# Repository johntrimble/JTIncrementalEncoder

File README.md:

# The JT Incremental Encoder
This is the Arduino source code for an optical rotary incremental encoder I built as a sort of hobby project. It provides 2-channel Quadrature output, as well as an I2C interface for calibration and reading position information.

## Dependencies
- Arduino IDE 1.5 or greater
- MCP4xxx library, available [here](https://github.com/johntrimble/MCP42xxx)
- g++ 4.2 or greater, this is just for the unit tests
- Make
- Git 1.6.5 or greater

## Building
This project uses submodules, so you'll want to do the following when cloning the repository:

```
git clone --recursive git@github.com:johntrimble/JTIncrementalEncoder.git
```

From there, just open the `JTIncrementalEncoder.ino` in the Arduino IDE and build it just like any other Arduino project.

## Unit Testing
Arduino doesn't have much in the way of support for unit testing code. Consequently, in the test folder there is a Makefile for building some native binaries to test the code. To run them, execute the following from the project root:

```
cd test
make
./interface_unittest && ./encoder_unittest
```

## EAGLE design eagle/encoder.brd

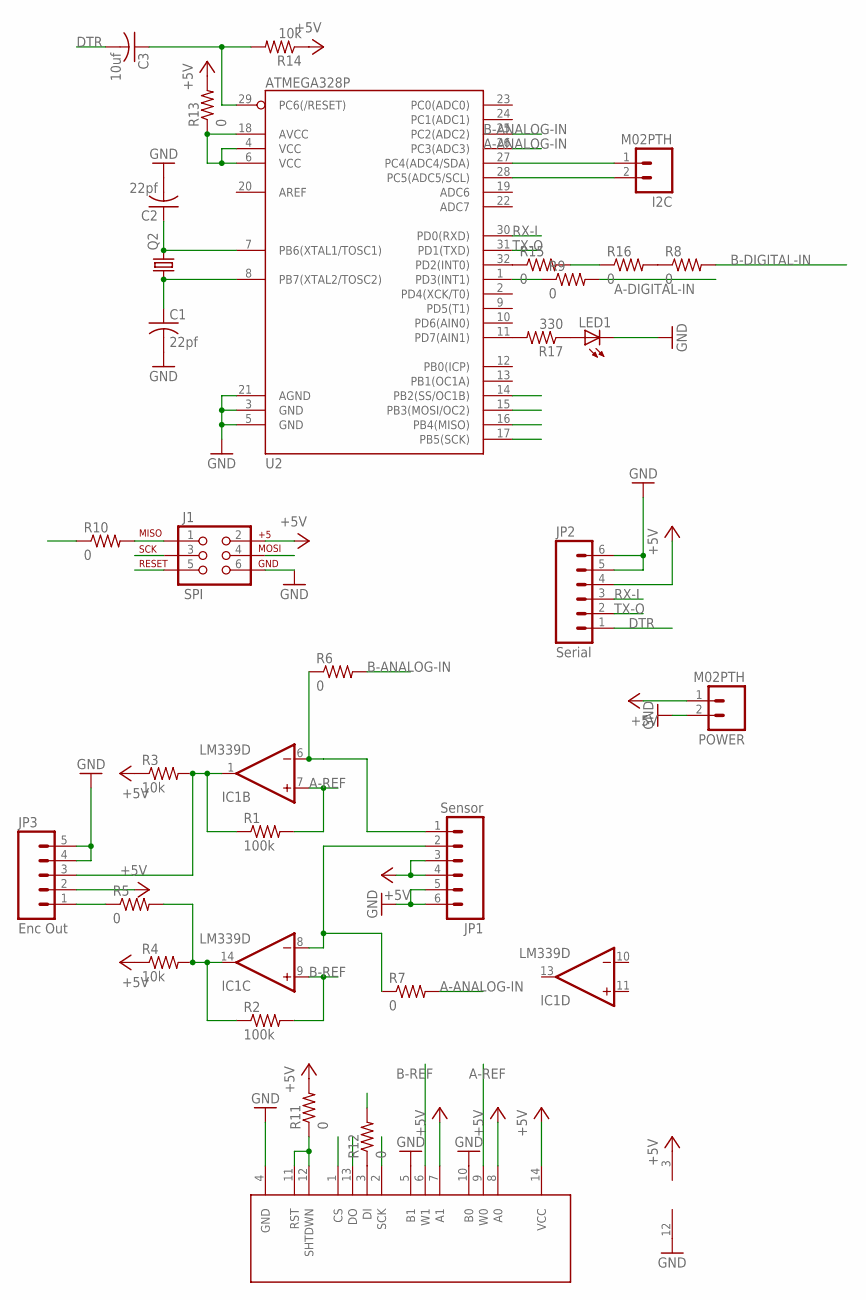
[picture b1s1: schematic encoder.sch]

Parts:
C1, C2: 22pf; C1206
C3: 10uf; C1206
I2C: M02PTH; 1X02
IC1: LM339D; SO14
J1: SPI; 2X3-NS
JP1: Sensor; 1X06
JP2: Serial; 1X06
JP3: Enc Out; 1X05_NO_SILK
LED1: LEDSMT1206; 1206
POWER: M02PTH; 1X02
Q2: CRYSTALHC49UP; HC49UP
R1, R2: 100k; R1206
R3, R4, R14: 10k; R1206
R5, R6, R7, R8, R9, R10, R11, R12, R13, R15, R16: 0; R1206
R17: 330; R1206
U1: MCP42XXX; SO014
U2: ATMEGA328P; TQFP32-08

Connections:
+5V: IC1.3 (V+), J1.2, JP1.3, JP1.4, JP2.4, JP3.2, POWER.1, R3.1, R4.1, R11.2, R13.2, R14.1, U1.7 (A1), U1.8 (A0), U1.14 (VCC)
A-ANALOG-IN: R7.2, U2.26 (PC3(ADC3))
A-DIGITAL-IN: IC1.1 (OUT), JP3.3, R1.1, R3.2, R9.2
A-REF: IC1.7 (+IN), R1.2, U1.9 (W0)
B-ANALOG-IN: R6.2, U2.25 (PC2(ADC2))
B-DIGITAL-IN: JP3.1, R5.1, R8.2
B-REF: IC1.9 (+IN), R2.2, U1.6 (W1)
DTR: C3.2, JP2.1
GND: C1.2, C2.2, IC1.12 (GND), J1.6, JP1.5, JP1.6, JP2.5, JP2.6, JP3.4, JP3.5, LED1.C, POWER.2, U1.4 (GND), U1.5 (B1), U1.10 (B0), U2.3 (GND), U2.5 (GND), U2.21 (AGND)
MISO: R10.1, U1.13 (DO), U2.16 (PB4(MISO))
MOSI: J1.4, R12.2, U2.15 (PB3(MOSI/OC2))
unnamed: IC1.8 (-IN), JP1.2, R7.1
unnamed: J1.1, R10.2
unnamed: IC1.6 (-IN), JP1.1, R6.1
unnamed: R11.1, U1.11 (RST), U1.12 (SHTDWN)
unnamed: IC1.14 (OUT), R2.1, R4.2, R5.2
unnamed: R15.1, U2.32 (PD2(INT0))
unnamed: R9.1, U2.1 (PD3(INT1))
unnamed: R12.1, U1.3 (DI)
unnamed: R13.1, U2.4 (VCC), U2.6 (VCC), U2.18 (AVCC)
unnamed: C1.1, Q2.1, U2.8 (PB7(XTAL2/TOSC2))
unnamed: C2.1, Q2.2, U2.7 (PB6(XTAL1/TOSC1))
unnamed: I2C.1, U2.27 (PC4(ADC4/SDA))
unnamed: I2C.2, U2.28 (PC5(ADC5/SCL))
unnamed: R15.2, R16.1
unnamed: R8.1, R16.2
unnamed: LED1.A, R17.1
unnamed: R17.2, U2.11 (PD7(AIN1))
RESET: C3.1, J1.5, R14.2, U2.29 (PC6(/RESET))
RX-I: JP2.3, U2.30 (PD0(RXD))
SCK: J1.3, U1.2 (SCK), U2.17 (PB5(SCK))
SS: U1.1 (CS), U2.14 (PB2(SS/OC1B))
TX-O: JP2.2, U2.31 (PD1(TXD))

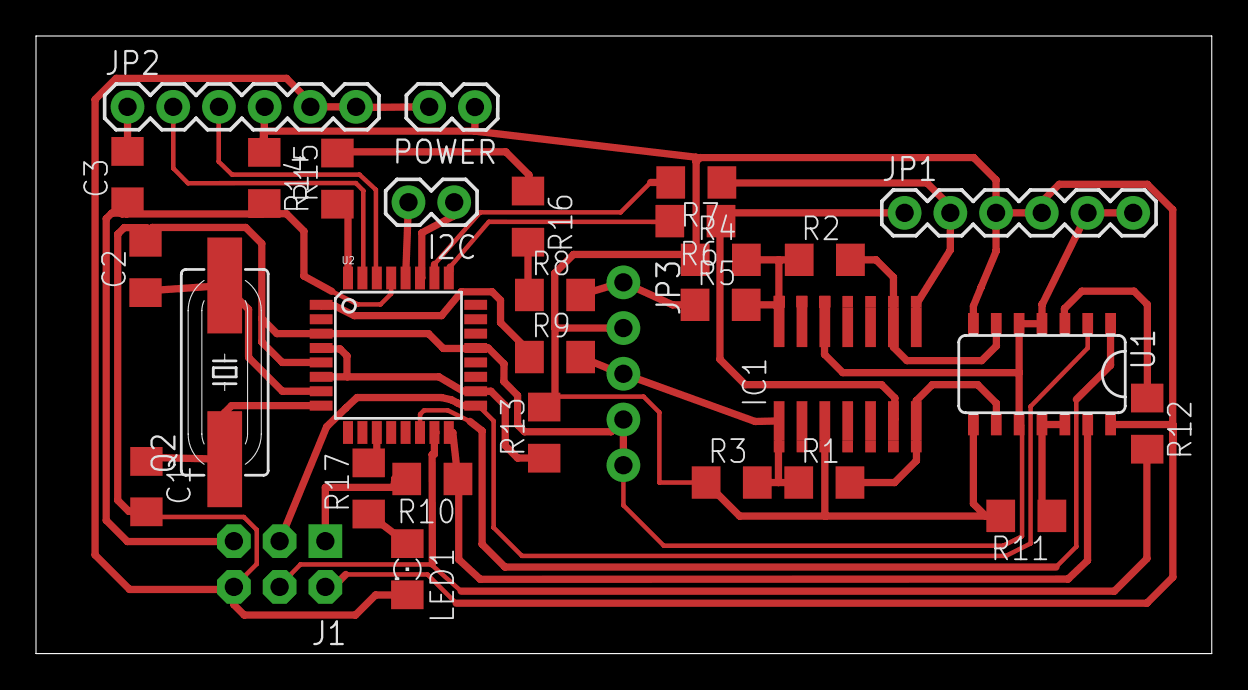
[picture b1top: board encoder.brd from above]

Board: 2 copper layers, 65.3 x 34.3 mm, 31 parts (0 on the bottom side), 33 nets.

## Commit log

2013-05-27 Initial commit.
2013-05-27 Update to allow tracking of position, not just steps taken.
2013-05-31 Added code to handle correctly updating wheel position when direction changes. Added basic I2C interface.
2013-06-01 Renamed project to something more specific.
2013-06-03 Updated to store settings in EEPROM.
2013-06-08 Changed voltage reference to midpoint between min and max. This used to use the average, but for some reason the midpoint between min and max works better. This is probably an issue with the average 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
2013-06-08 Fixed the scoping on some functions and global variables.
2013-06-08 Removed unused struct definition.
2013-06-08 Made some changes to way registers store data to be more compact.
2013-06-26 Added unit tests for encoder.cpp. Moved I2C interface out of encoder code proper.
2013-06-28 Added googlemock to project. Created Encoder class. Updated Interface to take and encoder object. Update some test cases to use the new Encoder class.
2013-06-30 Moved mocks to sutbs directory because that's what they are. Added test case for interface. Removed redundant code.
2013-07-06 Refactored EncoderInterface to use templates for the purpose of testing. Added unit tests for EncoderInterface. Refactored JTIncrementalEncoder.ino to use encoder and interface modules. Other minor u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
2013-11-24 Added constants.
2014-01-24 Fixed a spelling error. Fixed an inaccurate comment.
2014-01-24 Initial schematic and board layout with just the voltage comparator and digital pot.
2014-01-26 Added atmega.
2014-01-26 Added SPI hookup
2014-01-26 Added crystal.
2014-01-26 Added I2C and power connections.
2014-01-26 Moved components closer together
2014-01-26 Fixed an issue where the digital output channels were not connected to interrupts.
2014-01-26 Added LED indicator.
2014-01-27 Thinned some traces to provide sufficient clearance.
2014-01-27 Made corners 45 degrees as opposed to 90.
2014-01-27 Hacked pads for lm339 to be larger
2014-01-28 Fixed some additional corners to be 45 degrees instead of 90.
2014-02-07 Added a README.
2014-12-07 Minor borad layout updates.
2015-04-26 Updated PIN assignments
2015-04-26 WIP debugging
2015-05-02 WIP Refactoring calibration algorithm
2015-05-04 WIP Add tests and fix calibration
2015-05-10 WIP new calibration algorithm
2015-06-23 Replace digital POT with PWM for reference voltage
    In an effort to simplify the circuit board, the digital POT has been replaced
    by the use of PWM for the reference voltage. The calibration algorithm has also
    been updated obviating the need to use the Arduino's analog inputs to determine
    the appropriate reference voltage setting. Instead, the algorithm now
    determines an appropriate reference voltage by measuring the dutycycle of the
    signal out of the voltage comparator.

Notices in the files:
parts and their libraries:
SparkFun-AnalogIC: Licensing: CC v3.0 Share-Alike You are welcome to use this library for commercial purposes.
